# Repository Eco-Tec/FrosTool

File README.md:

## FrosTool
Herramienta de monitoreo de variables climaticas para la generación de alertas tempranas para mitiga los efectos de las heladas en los cultivos del departamento de Boyaca- Col

# Arbol de directorios
- 3D-Model: Diseños de lo relacionado con las sondas, cajas, soportes, etc.
- Articulo: Contiene un Articulo cort ode investigación enformato IEEE.
- Docs: Contiene la documentación o linkeos hacia la misma (Texto, links, Imagenes)
- Hardware: Referente al hardware desarrollado (Esquemas, PCBs)
- Images: Aqui colocar imagenes solamente referente a el desarrollo del proyecto.
- Software: Principalmente el codigo desarrollado para el proeycto.

# Attributions
Basada en la idea de 
Fabián Andrés Salamanca Figueroa, Willmar Arbey Suarez Rodriguez, Christian Camilo Cárdenas Gamboa
https://github.com/fandres/Monitor-heladas

Este Proyecto
- @fandres
- @maurinc2010

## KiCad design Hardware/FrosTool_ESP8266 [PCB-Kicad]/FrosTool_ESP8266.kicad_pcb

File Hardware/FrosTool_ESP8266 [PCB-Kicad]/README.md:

# Model 3D on FreeCad
============

License 
======

[Creative Commons Attribution-ShareAlike 4.0 International License](http://creativecommons.org/licenses/by-sa/4.0/)

Attributions
============
See commit details to find the authors of each Part.
- @fandres
- @maurinc2010

Schematic symbols and PCB footprints for ESP8266 modules 
- Copyright 2015,2016 J.Dunmire, kicad-ESP8266 is licensed under the Creative Commons Attribution-ShareAlike
4.0 International License. To view a copy of this license visit
http://creativecommons.org/licenses/by-sa/4.0/.

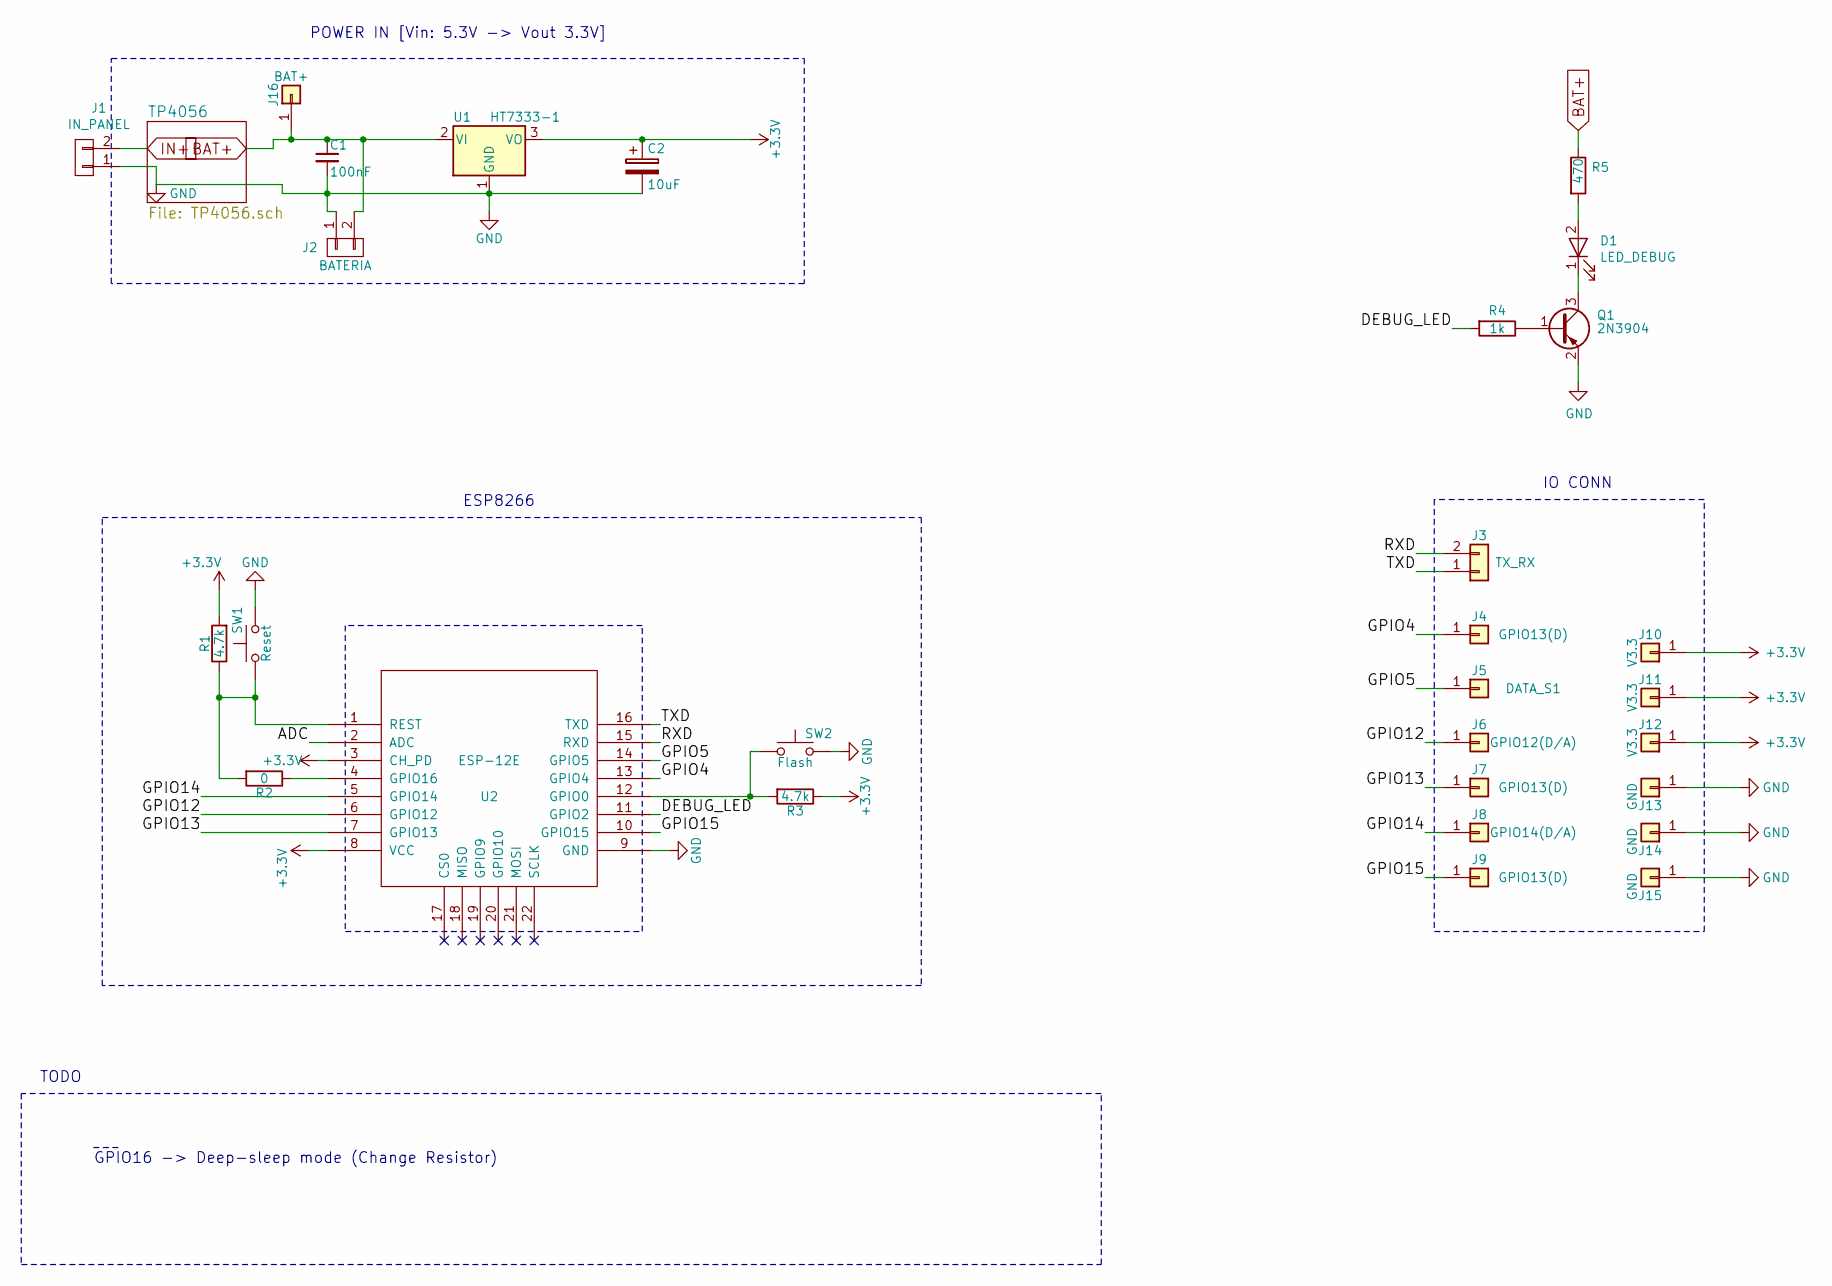
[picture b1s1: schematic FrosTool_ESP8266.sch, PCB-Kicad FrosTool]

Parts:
C1: 100nF; C_0805
C2: 10uF; c_elec_4x5.3
D1: LED_DEBUG; LED-3MM
J1: IN_PANEL; Pin_Header_Straight_1x02_Pitch2.00mm
J2: BATERIA; Pin_Header_Straight_1x02_Pitch2.00mm
J3: TX_RX; Pin_Header_Straight_1x02_Pitch2.00mm
J4, J7, J9: GPIO13(D); Pin_Header_Straight_1x01
J5: DATA_S1; Pin_Header_Straight_1x01
J6: GPIO12(D/A); Pin_Header_Straight_1x01
J8: GPIO14(D/A); Pin_Header_Straight_1x01
J10, J11, J12: V3.3; Pin_Header_Straight_1x01
J13, J14, J15: GND; Pin_Header_Straight_1x01
J16: BAT+; Pin_Header_Straight_1x01
Q1: 2N3904; SOT-23
R1, R3: 4.7k; R_1206
R2: 0; R_1206
R4: 1k; R_1206
R5: 470; R_1206
SW1: Reset; SW_SPST_B3U-1000P
SW2: Flash; SW_SPST_B3U-1000P
U1: HT7333-1; SOT89-3_Housing
U2: ESP-12E; ESP-12E_SMD

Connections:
+3V3: C2.1, J10.1, J11.1, J12.1, R1.2, R3.1, U1.3 (VO), U2.3 (CH_PD), U2.8 (VCC)
/ADC: U2.2 (ADC)
/DEBUG_LED: R4.2, U2.11 (GPIO2)
/GPIO4: J4.1, U2.13 (GPIO4)
/GPIO5: J5.1, U2.14 (GPIO5)
/GPIO12: J6.1, U2.6 (GPIO12)
/GPIO13: J7.1, U2.7 (GPIO13)
/GPIO14: J8.1, U2.5 (GPIO14)
/GPIO15: J9.1, U2.10 (GPIO15)
/RXD: J3.2, U2.15 (RXD)
/TXD: J3.1, U2.16 (TXD)
BAT+: C1.1, J2.2, J16.1, R5.1, U1.2 (VI); also elsewhere on the board
GND: C1.2, C2.2, J1.1, J2.1, J13.1, J14.1, J15.1, Q1.2 (E), SW1.2, SW2.2, U1.1 (GND), U2.9 (GND); also elsewhere on the board
IN+: J1.2; also elsewhere on the board
unnamed: D1.1 (K), Q1.3 (C)
unnamed: D1.2 (A), R5.2
unnamed: Q1.1 (B), R4.1
unnamed: R1.1, R2.2, SW1.1, U2.1 (REST)
unnamed: R2.1, U2.4 (GPIO16)
unnamed: R3.2, SW2.1, U2.12 (GPIO0)

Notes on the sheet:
POWER IN [Vin: 5.3V -> Vout 3.3V]
TODO
GPIO16 -> Deep-sleep mode (Change Resistor)
ESP8266
IO CONN

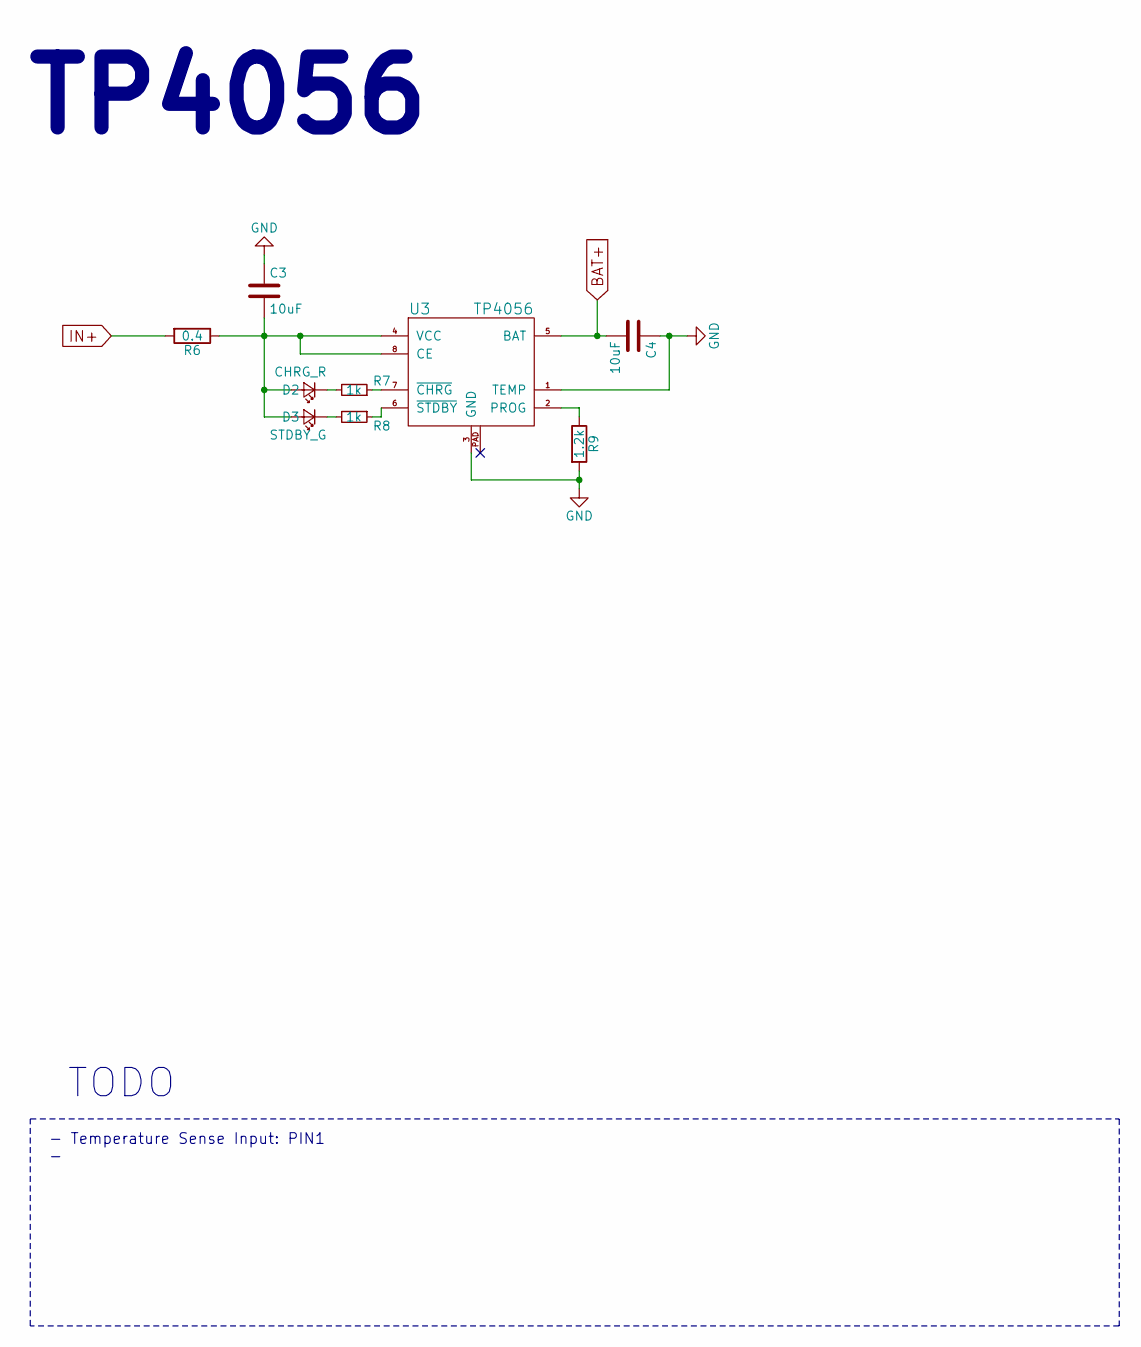
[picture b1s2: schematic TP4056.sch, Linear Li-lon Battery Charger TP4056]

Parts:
C3: 10uF; c_elec_4x5.3
C4: 10uF; C_0805
D2: CHRG_R; LED-3MM
D3: STDBY_G; LED-3MM
R6: 0.4; R_1206
R7, R8: 1k; R_1206
R9: 1.2k; R_1206
U3: TP4056; SOIC-8_3.9x4.9mm_Pitch1.27mm

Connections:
BAT+: C4.2, U3.5 (BAT); also elsewhere on the board
GND: C3.1, C4.1, R9.2, U3.1 (TEMP), U3.3 (GND); also elsewhere on the board
IN+: R6.2; also elsewhere on the board
unnamed: C3.2, D2.2 (A), D3.2 (A), R6.1, U3.4 (VCC), U3.8 (CE)
unnamed: D2.1 (K), R7.2
unnamed: D3.1 (K), R8.2
unnamed: R7.1, U3.7 (~CHRG)
unnamed: R8.1, U3.6 (~STDBY)
unnamed: R9.1, U3.2 (PROG)

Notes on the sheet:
- Temperature Sense Input: PIN1 -
TODO
TP4056

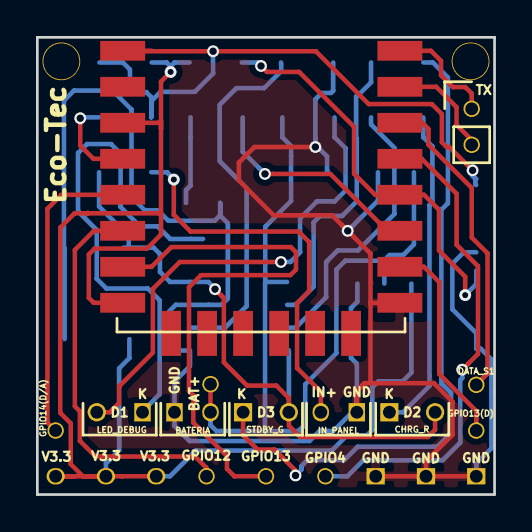
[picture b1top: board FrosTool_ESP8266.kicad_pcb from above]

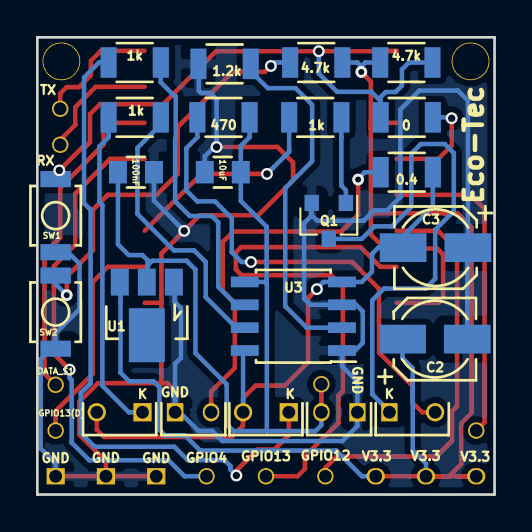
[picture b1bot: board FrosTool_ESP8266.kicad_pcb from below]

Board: 2 copper layers, 25.4 x 25.4 mm, 40 parts (18 on the bottom side), 25 nets.

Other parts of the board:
Drill2mm_1, Drill222_2: SolderWirePad_single_1-2mmDrill

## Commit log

2017-08-08 Modified readme.md. Attributions and basic description.
2017-08-08 Upload Article.
2017-08-08 Added Docs
2017-08-09 Aggregated tables
2017-09-02 Update Docs 1
2017-09-16 froked and reestructured(Wifi, MQTT)
2017-09-16 Update Datasheet link
2017-09-16 Upload new firmware microPython 1.9.2 stable version
2017-09-24 Config Local
2017-09-24 Codigo de sonda usando clases
2017-09-24 Update path
2017-09-24 Ignore files
2017-09-25 Added Mode Debug
2017-09-25 Addes Class DHT22 (Module: sensores)
2017-09-25 Clase para gestionar el modo debug
2017-09-26 Cambios a la clase DTH22
2017-09-26 PEP-8 and os.debug(UART0)
2017-09-26 Manejo de varios sensores declarados desde config.py
2017-09-26 Added: MQTT Debug update: method debugMode
2017-09-26 imports PEP-8 printDebugMode
2017-09-26 Modificación de clase cultivo para enviar datos usado MQTT
2017-09-26 PEP-8
2017-09-26 Phythonic Code (PEP-8)
2017-09-26 Bug Fixed (Debug On/Off)
2017-09-27 Added 3D-Model (sketch): Sonda
2017-09-27 Created Sketch PCB
2017-10-04 Added Schematic: libraries, power and sensors
2017-10-06 Add sistema de carga al esquematico
2017-10-08 Added sheet Linear Li-lon Battery Charger
2017-10-08 Design proposal Node_1
2017-10-09 ESP8266 Mod Prog
2017-10-09 Added Pin Diagram (ESP8266)
2017-10-09 IO CONN
2017-10-11 Removed the old TP4056 component
2017-10-11 Added NETList
2017-10-12 Footprints
2017-10-12 Rules Design Drill Pads
2017-10-13 components located
2017-10-13 AutoRuting
2017-10-14 Tracks and Vias improvement Bug Fixed: Pads Regulator
2017-10-14 Added Schematic
2017-10-14 Added zones (F.cu, B.cu -> GND)
2017-10-17 F.Fab, B.Fab
2017-10-17 Added Pin Extra: BAT+
2017-10-22 Model PCB FrosToolESP8266
2017-10-22 Sketch
2017-10-23 Model Case: Revolution
2017-10-24 Bug Fixed: Mode Debug -> unsupported type error
2017-10-24 Upgraded debug messages
2017-10-24 Added proposed Node
2017-10-28 Added proposal 2 node
2017-10-30 Visual Debug Added parameter to the printDebug method
2017-11-01 device to sleep (deep sleep)
2017-11-21 Added STATUS LED
2017-11-21 Added LICENCE, sketch and ignore files
2017-11-22 Update Ignore Files. Added Firmware
2017-12-13 Plantilla para almacenado de los datos
2017-12-18 Generacion de archivos csv
2017-12-20 Archivo de configuación del broker
2017-12-20 Software broker 1.4, gestion de informes y control de accesos de topicos no autorizado
2017-12-20 Change config: Topics
2017-12-20 Update Firmware
2017-12-27 Lectura y guardado del estado del bootloader
2017-12-27 Update gitignore file - swap - frecad backup
2017-12-27 manual CLient_ID RTC Ajust
2017-12-27 Credits
2017-12-27 Case Sensors, STL format
2017-12-28 Secure the Wi-Fi connection before the MQTT connection
2017-12-28 Test de bootloader
2017-12-28 Modificación bootloader
2017-12-28 MQTT: Data received
2017-12-29 Modificación de la clase MQTT para mantener abierta la suscripcion asta que se termine la transmicion y recepcion de todos los datos
2018-01-10 Except OSError Problem
2018-01-10 pre1, PEP-8
2018-01-10 error file read: syntax
2018-01-10 debug mode display
2018-01-11 Update config file update gitignore file
2018-01-12 MQTT: user/password authentication
2018-01-21 Solución problema de conexion wifi
2018-01-21 Transmicion de archivos usando socket
2018-01-22 - Implemented authentication by user and password. For the client used to manage the Broker (Orange PI) - Change from "localhost" to manual ip configuration: "localhost" -> "192.168.42"
2018-01-23 Wi-Fi and MQTT network files deleted
2018-01-23 Implemented basic file storage
2018-01-29 Model Support. Added STL parts
2018-03-08 Aggregates 3D Models: Esp8266 (by Christophe Chaloin) and model adapted by fandres of ILI9341-2_8 (by Christophe Chaloin)
2018-03-08 3D Models Added and relocated, part 1.
2018-03-08 Added Stencil
2018-03-10 Ignore Design temp
2018-03-20 Added Model: Case Broker
2018-03-30 Widget para pantalla 2.4 pulgadas
2018-04-01 Drill 0,8 mm FrosTool And Eco-Tec
2018-04-20 Added RTC: Date and Time
2018-05-29 Bug Fixed (R10k x2), No Programing, Debug_led(USERLED)
